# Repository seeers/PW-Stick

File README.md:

**[PW-Stick](https://github.com/seeers/PW-Stick)** is a easy to use hardware password manager
======

## Features
* Stores up to 9 user names and passwords / each up to 47 characters
* Keepass 2 (http://keepass.info/) supports the PW-Stick with a plugin
* AES Encrypted Memory
* Protected by a 4 digit pin
* Secure erase after 4 wrong pin attempts
* Optional auto lock timer
* Works as HID Keyboard

## Portable version

## Desktop version

## Instructions

See the wiki for build and use instructions.

## Notes
**Released:** 
* Stick version by Seeers : Mar 23, 2016
* Desktop version by MatthGyver : Apr 07, 2019

**Status:** Operational, maybe some bugs, works for me since some months.

**Licence:**  CC BY-NC-SA 3.0

## Contact
**Point of Contact:**  
* Twitter: [@seeers0](https://twitter.com/seeers0)
* E-Mail: <seeers@gmx.de>

-----

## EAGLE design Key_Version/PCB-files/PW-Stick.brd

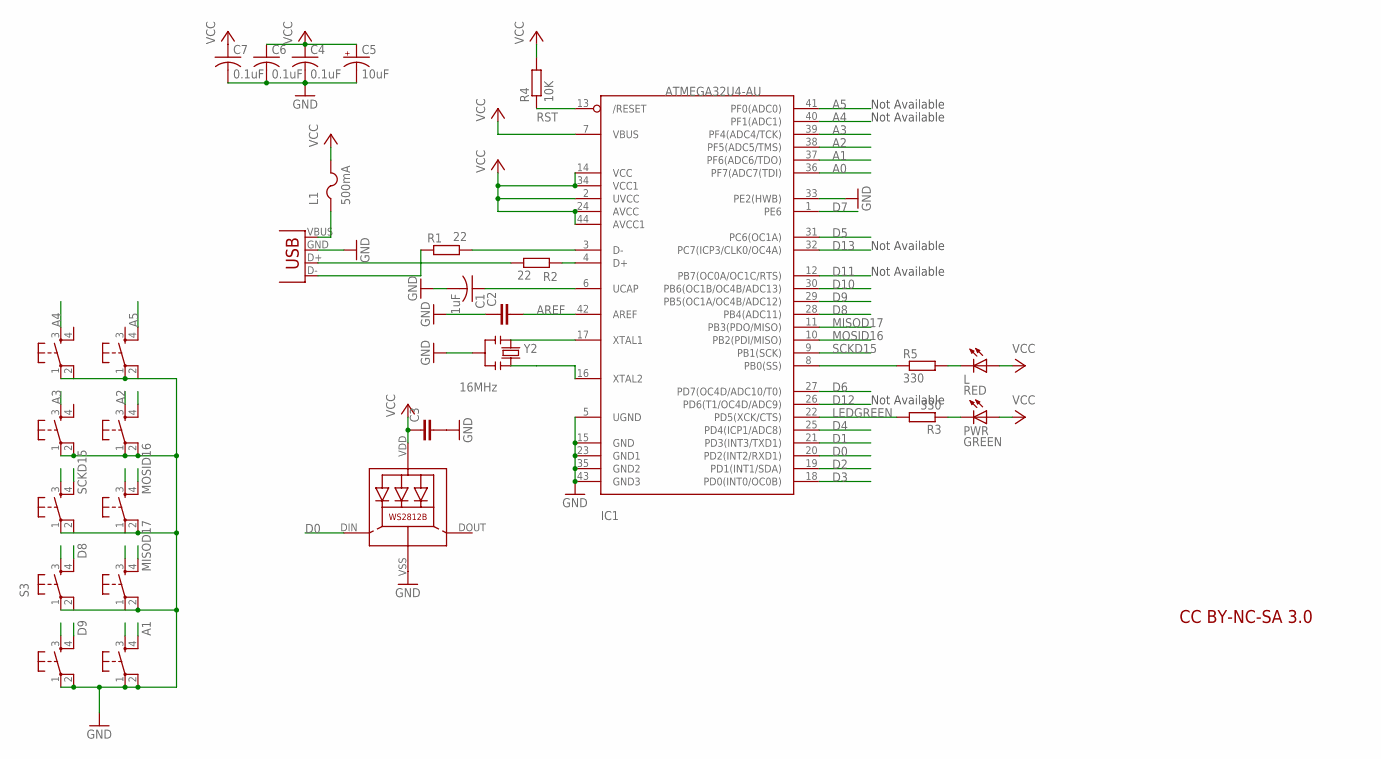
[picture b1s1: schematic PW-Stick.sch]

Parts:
C1: 1uF; C0805K
C2, C3: C-EUC0805; C0805
C4, C6, C7: 0.1uF; C0805K
C5: 10uF; A/3216-18R
IC1: ATMEGA32U4-AU; TQFP44
JP2: USB-A-H
L: RED; CHIPLED_0805
L1: 500mA; R1206
LED1: WS2812B
PWR: GREEN; CHIPLED_0805
R1, R2: 22; R0805
R3, R5: 330; R0805
R4: 10K; R0805
S1, S2, S3, S4, S5, S6, S7, S8, S9, S10: DTSM-6
Y2: 16MHz; RESONATOR

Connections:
A0: IC1.36 (PF7(ADC7(TDI))
A1: IC1.37 (PF6(ADC6/TDO)), S2.4
A2: IC1.38 (PF5(ADC5/TMS)), S8.3
A3: IC1.39 (PF4(ADC4/TCK)), S7.3
A4: IC1.40 (PF1(ADC1)), S9.3
A5: IC1.41 (PF0(ADC0)), S10.4
AREF: C2.2, IC1.42 (AREF)
D0: IC1.20 (PD2(INT2/RXD1)), LED1.DIN (DI)
D1: IC1.21 (PD3(INT3/TXD1))
D2: IC1.19 (PD1(INT1/SDA))
D3: IC1.18 (PD0(INT0/OC0B))
D4: IC1.25 (PD4(ICP1/ADC8))
D5: IC1.31 (PC6(OC1A))
D6: IC1.27 (PD7(OC4D/ADC10/T0))
D7: IC1.1 (PE6)
D8: IC1.28 (PB4(ADC11)), S3.4
D9: IC1.29 (PB5(OC1A/OC4B/ADC12)), S1.4
D10: IC1.30 (PB6(OC1B/OC4B/ADC13))
D11: IC1.12 (PB7(OC0A/OC1C/RTS))
D12: IC1.26 (PD6(T1/OC4D/ADC9))
D13: IC1.32 (PC7(ICP3/CLK0/OC4A))
GND: C1.2, C2.1, C3.2, C4.2, C5.-, C6.2, C7.2, IC1.5 (UGND), IC1.15 (GND), IC1.23 (GND1), IC1.33 (PE2(HWB)), IC1.35 (GND2), IC1.43 (GND3), JP2.GND (VBUS), LED1.VSS (GND), S1.1, S1.2, S2.1, S2.2, S3.1, S4.2, S5.1, S6.2, S7.1, S7.2, S8.1, S8.2, S9.1, S10.1, Y2.2
LEDGREEN: IC1.22 (PD5(XCK/CTS)), R3.2
MISOD17: IC1.11 (PB3(PDO/MISO)), S4.4
MOSID16: IC1.10 (PB2(PDI/MISO)), S6.3
unnamed: PWR.C, R3.1
unnamed: JP2.D+ (D-), R2.1
unnamed: IC1.3 (D-), R1.2
unnamed: IC1.4 (D+), R2.2
unnamed: JP2.D- (D+), R1.1
unnamed: IC1.8 (PB0(SS)), R5.1
unnamed: L.C, R5.2
unnamed: IC1.17 (XTAL1), Y2.1
unnamed: IC1.16 (XTAL2), Y2.3
unnamed: C1.1, IC1.6 (UCAP)
RST: IC1.13 (/RESET), R4.1
SCKD15: IC1.9 (PB1(SCK)), S5.3
VBUS: JP2.VBUS (GND), L1.1
VCC: C3.1, C4.1, C5.+, C6.1, C7.1, IC1.2 (UVCC), IC1.7 (VBUS), IC1.14 (VCC), IC1.24 (AVCC), IC1.34 (VCC1), IC1.44 (AVCC1), L.A, L1.2, LED1.VDD, PWR.A, R4.2

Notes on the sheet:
CC BY-NC-SA 3.0
Not Available

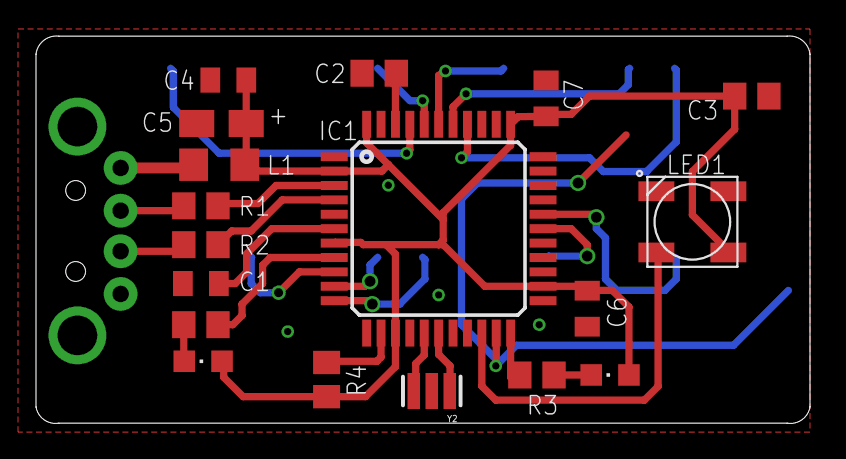
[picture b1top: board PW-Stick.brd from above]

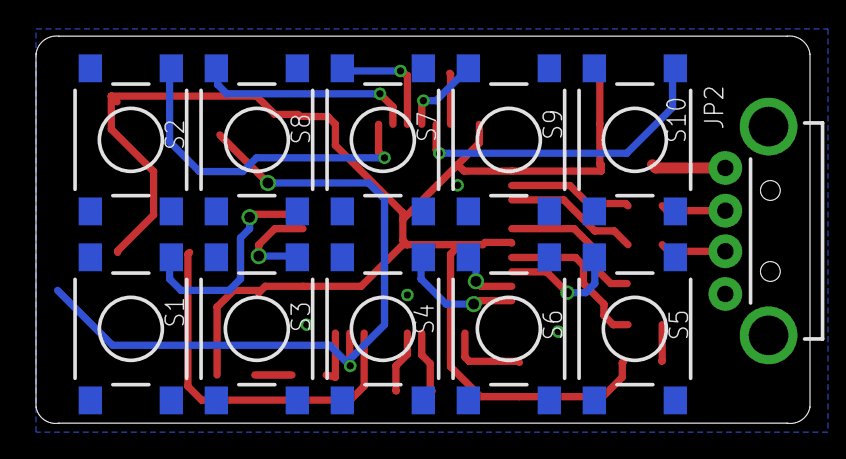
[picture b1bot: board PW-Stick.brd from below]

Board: 2 copper layers, 43.0 x 21.5 mm, 29 parts (11 on the bottom side), 27 nets.

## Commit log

2016-03-23 Added files via upload
2016-03-24 Create LICENSE
2016-03-24 bold format
2016-03-24 some notes
2016-03-24 structural changes
2016-03-24 Add english keyboard layout
2016-03-29 upload schematic
2016-03-29 Add schematic
2016-03-29 some changes
2016-03-29 Cleanup
2016-03-29 documentation
2017-10-15 Add French Azerty Keyboard
2018-04-22 create desktop version and adapt main readme
2018-04-22 add some instructions
2018-04-22 flash led factorization
2018-04-22 small modifications
2018-04-22 syntax correction
2018-05-03 Fix Bug on long press
2018-05-13 Update Source_code.ino
    Fix bug on long press
2018-06-19 Update README.md
    Modify KeePass download link
2019-04-07 restructuration
2019-04-07 minor update
2019-04-07 add board files

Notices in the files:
parts and their libraries:
SparkFun-Connectors: Licensing: Creative Commons ShareAlike 4.0 International - https://creativecommons.org/licenses/by-sa/4.0
